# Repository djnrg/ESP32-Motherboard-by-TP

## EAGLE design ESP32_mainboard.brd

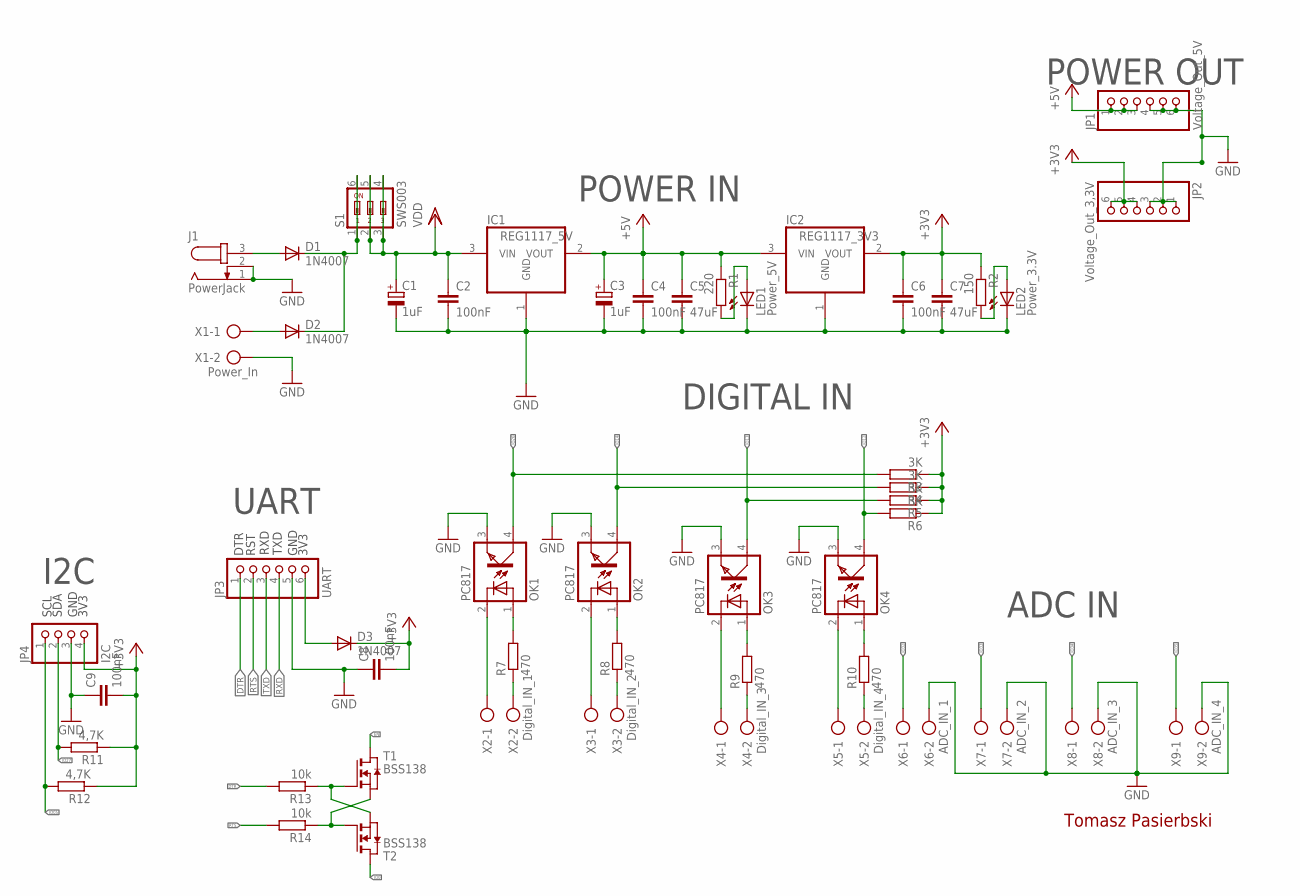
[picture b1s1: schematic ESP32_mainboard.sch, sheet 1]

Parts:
C1, C3: 1uF; 140CLH-0810
C2, C4, C6, C8, C9: 100nF; C1206
C5, C7: 47uF; C1808
D1, D2, D3: 1N4007; DO214AA
IC1: REG1117_5V; SOT223
IC2: REG1117_3V3; SOT223
J1: PowerJack; SPC4077
JP1: Voltage_Out_5V; 1X06/90
JP2: Voltage_Out_3,3V; 1X06/90
JP3: UART; 1X06/90
JP4: I2C; 1X04/90
LED1: Power_5V; CHIPLED_1206
LED2: Power_3.3V; CHIPLED_1206
OK1, OK2, OK3, OK4: PC817; DIL04
R1: 220; M1206
R2: 150; M1206
R3, R4, R5, R6: 3K; M1206
R7, R8, R9, R10: 470; M1206
R11, R12: 4,7K; M1206
R13, R14: 10k; M1206
S1: SWS003; SMS-003
T1, T2: BSS138; SOT-23
X1: Power_In; AK300/2
X2: Digital_IN_1; AK300/2
X3: Digital_IN_2; AK300/2
X4: Digital_IN_3; AK300/2
X5: Digital_IN_4; AK300/2
X6: ADC_IN_1; AK300/2
X7: ADC_IN_2; AK300/2
X8: ADC_IN_3; AK300/2
X9: ADC_IN_4; AK300/2

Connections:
+3V3: C6.1, C7.1, C8.2, C9.2, D3.C, IC2.2 (VOUT), JP2.4, JP2.5, JP2.6, JP4.4, R2.1, R3.1, R4.1, R5.1, R6.1, R11.1, R12.1; also elsewhere on the board
+5V: C3.+, C4.1, C5.1, IC1.2 (VOUT), IC2.3 (VIN), JP1.1, JP1.2, JP1.3, R1.1; also elsewhere on the board
DTR: JP3.1, R13.2
EN: T1.1 (D); also elsewhere on the board
GND: C1.-, C2.2, C3.-, C4.2, C5.2, C6.2, C7.2, C8.1, C9.1, IC1.1 (GND), IC2.1 (GND), J1.1, J1.2, JP1.4, JP1.5, JP1.6, JP2.1, JP2.2, JP2.3, JP3.5, JP4.3, LED1.C, LED2.C, OK1.3 (EMIT), OK2.3 (EMIT), OK3.3 (EMIT), OK4.3 (EMIT), X1.2, X6.2, X7.2, X8.2, X9.2; also elsewhere on the board
IO0: T2.1 (D); also elsewhere on the board
IO05: JP4.1, R12.2; also elsewhere on the board
IO12: OK4.4 (COL), R6.2; also elsewhere on the board
IO13: OK3.4 (COL), R5.2; also elsewhere on the board
IO14: OK2.4 (COL), R4.2; also elsewhere on the board
IO26: OK1.4 (COL), R3.2; also elsewhere on the board
IO27: JP4.2, R11.2; also elsewhere on the board
IO32: X6.1; also elsewhere on the board
IO33: X7.1; also elsewhere on the board
IO34: X8.1; also elsewhere on the board
IO35: X9.1; also elsewhere on the board
unnamed: D1.A, J1.3
unnamed: D1.C, D2.C, S1.1, S1.6
unnamed: D2.A, X1.1
unnamed: D3.A, JP3.6
unnamed: LED1.A, R1.2
unnamed: LED2.A, R2.2
unnamed: OK3.2 (C), X4.1
unnamed: OK3.1 (A), R9.2
unnamed: OK1.2 (C), X2.1
unnamed: R13.1, T1.3 (G), T2.2 (S)
unnamed: R14.1, T1.2 (S), T2.3 (G)
unnamed: R9.1, X4.2
unnamed: OK4.2 (C), X5.1
unnamed: OK4.1 (A), R10.2
unnamed: R10.1, X5.2
unnamed: OK2.2 (C), X3.1
unnamed: OK2.1 (A), R8.2
unnamed: R8.1, X3.2
unnamed: OK1.1 (A), R7.2
unnamed: R7.1, X2.2
RTS: JP3.2, R14.2
RXD: JP3.4; also elsewhere on the board
TXD: JP3.3; also elsewhere on the board
VDD: C1.+, C2.1, IC1.3 (VIN), S1.2, S1.3, S1.4, S1.5; also elsewhere on the board

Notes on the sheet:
I2C
UART
POWER OUT
POWER IN
ADC IN
DIGITAL IN
SDA
SCL
GND
3V3
RST
DTR
RXD
TXD
Tomasz Pasierbski

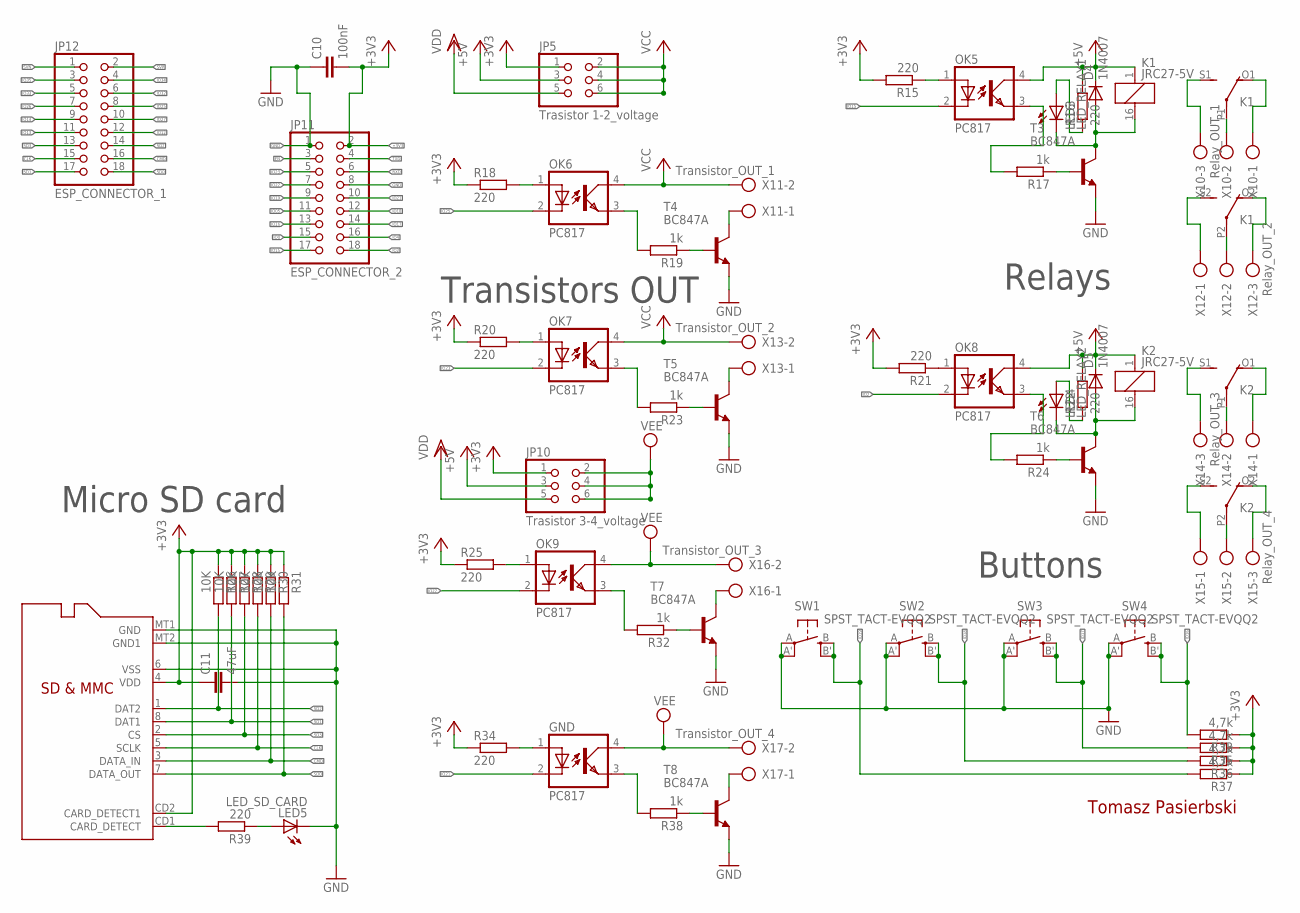
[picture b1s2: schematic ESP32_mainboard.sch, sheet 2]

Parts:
C10: 100nF; C1206
C11: 47uF; C1808
D4, D5: 1N4007; DO214AC
GND: PC817; DIL04
JP5: Trasistor 1-2_voltage; 2X03
JP10: Trasistor 3-4_voltage; 2X03
JP11: ESP_CONNECTOR_2; 2X09
JP12: ESP_CONNECTOR_1; 2X09
K1, K2: JRC27-5V; 351
LED3: LED_RELAY1; CHIPLED_1206
LED4: LED_RELAY2; CHIPLED_1206
LED5: LED_SD_CARD; CHIPLED_1206
OK5, OK6, OK7, OK8, OK9: PC817; DIL04
R15, R16, R18, R20, R21, R22, R25, R34, R39: 220; M1206
R17, R19, R23, R24, R32, R38: 1k; M1206
R26, R27, R28, R29, R30, R31: 10K; M1206
R33, R35, R36, R37: 4,7k; M1206
SW1, SW2, SW3, SW4: SPST_TACT-EVQQ2; EVQ-Q2
T3, T4, T5, T6, T7, T8: BC847A; SOT23-BEC
U2: MICROSD
X10: Relay_OUT_1; AK300/3
X11: Transistor_OUT_1; AK300/2
X12: Relay_OUT_2; AK300/3
X13: Transistor_OUT_2; AK300/2
X14: Relay_OUT_3; AK300/3
X15: Relay_OUT_4; AK300/3
X16: Transistor_OUT_3; AK300/2
X17: Transistor_OUT_4; AK300/2

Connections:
+3V3: C10.2, C11.1, JP5.1, JP10.1, JP11.2, R15.2, R18.1, R20.1, R21.2, R25.1, R26.1, R27.1, R28.1, R29.1, R30.1, R31.1, R33.1, R34.1, R35.1, R36.1, R37.1, U2.4 (VDD), U2.CD2 (CARD_DETECT1); also elsewhere on the board
+5V: D4.C, D5.C, JP5.3, JP10.3, K1.1, K2.1, OK5.4 (COL), OK8.4 (COL), R16.2, R22.2; also elsewhere on the board
CLK: JP12.15, R29.2, U2.5 (SCLK)
CMD: JP12.16, R30.2, U2.3 (DATA_IN)
EN: JP11.3; also elsewhere on the board
GND: C10.1, C11.2, JP11.1, JP11.8, LED5.C, SW1.A, SW1.A' (P1), SW2.A, SW2.A' (P1), SW3.A, SW3.A' (P1), SW4.A, SW4.A' (P1), T3.E, T4.E, T5.E, T6.E, T7.E, T8.E, U2.6 (VSS), U2.MT1 (GND), U2.MT2 (GND1); also elsewhere on the board
IO0: JP11.15; also elsewhere on the board
IO2: JP11.18, OK8.2 (C)
IO4: JP11.16
IO05: JP11.11; also elsewhere on the board
IO12: JP12.12; also elsewhere on the board
IO13: JP12.11; also elsewhere on the board
IO14: JP12.9; also elsewhere on the board
IO15: JP11.17, OK5.2 (C)
IO16: JP11.13, R33.2, SW4.B (S), SW4.B' (S1)
IO17: JP11.14, R35.2, SW3.B (S), SW3.B' (S1)
IO18: JP11.12, R36.2, SW2.B (S), SW2.B' (S1)
IO19: JP11.9, R37.2, SW1.B (S), SW1.B' (S1)
IO21: GND.2 (C), JP11.10
IO22: JP11.7, OK9.2 (C)
IO23: JP11.5, OK7.2 (C)
IO25: JP12.8, OK6.2 (C)
IO26: JP12.7; also elsewhere on the board
IO27: JP12.10; also elsewhere on the board
IO32: JP12.6; also elsewhere on the board
IO33: JP12.5; also elsewhere on the board
IO34: JP12.4; also elsewhere on the board
IO35: JP12.3; also elsewhere on the board
unnamed: K1.S1 (S), X10.3
unnamed: K1.O1 (O), X10.1
unnamed: K1.P1, X10.2
unnamed: K1.S2 (S), X12.1
unnamed: K1.P2, X12.2
unnamed: K1.O2 (O), X12.3
unnamed: K2.O1 (O), X14.1
unnamed: K2.S1 (S), X14.3
unnamed: K2.P1, X14.2
unnamed: K2.S2 (S), X15.1
unnamed: K2.O2 (O), X15.3
unnamed: K2.P2, X15.2
unnamed: OK8.1 (A), R21.1
unnamed: OK5.1 (A), R15.1
unnamed: R17.1, T3.B
unnamed: OK5.3 (EMIT), R17.2
unnamed: OK8.3 (EMIT), R24.2
unnamed: D4.A, K1.16 (2), LED3.C, T3.C
unnamed: R24.1, T6.B
unnamed: LED3.A, R16.1
unnamed: OK6.1 (A), R18.2
unnamed: OK7.1 (A), R20.2
unnamed: D5.A, K2.16 (2), LED4.C, T6.C
unnamed: LED4.A, R22.1
unnamed: R19.1, T4.B
unnamed: OK6.3 (EMIT), R19.2
unnamed: R39.2, U2.CD1 (CARD_DETECT)
unnamed: T4.C, X11.1
unnamed: R23.1, T5.B
unnamed: OK7.3 (EMIT), R23.2
unnamed: T5.C, X13.1
unnamed: LED5.A, R39.1
unnamed: OK9.1 (A), R25.2
unnamed: R32.1, T7.B
unnamed: OK9.3 (EMIT), R32.2
unnamed: T7.C, X16.1
unnamed: GND.1 (A), R34.2
unnamed: R38.1, T8.B
unnamed: GND.3 (EMIT), R38.2
unnamed: T8.C, X17.1
RXD: JP11.6; also elsewhere on the board
SD0: JP12.18, R31.2, U2.7 (DATA_OUT)
SD1: JP12.17, R27.2, U2.8 (DAT1)
SD2: JP12.14, R26.2, U2.1 (DAT2)
SD3: JP12.13, R28.2, U2.2 (CS)
SVN: JP12.1
SVP: JP12.2
TXD: JP11.4; also elsewhere on the board
VCC: JP5.2, JP5.4, JP5.6, OK6.4 (COL), OK7.4 (COL), X11.2, X13.2
VDD: JP5.5, JP10.5; also elsewhere on the board
VEE: GND.4 (COL), JP10.2, JP10.4, JP10.6, OK9.4 (COL), X16.2, X17.2

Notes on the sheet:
Buttons
Relays
Transistors OUT
Micro SD card
Tomasz Pasierbski

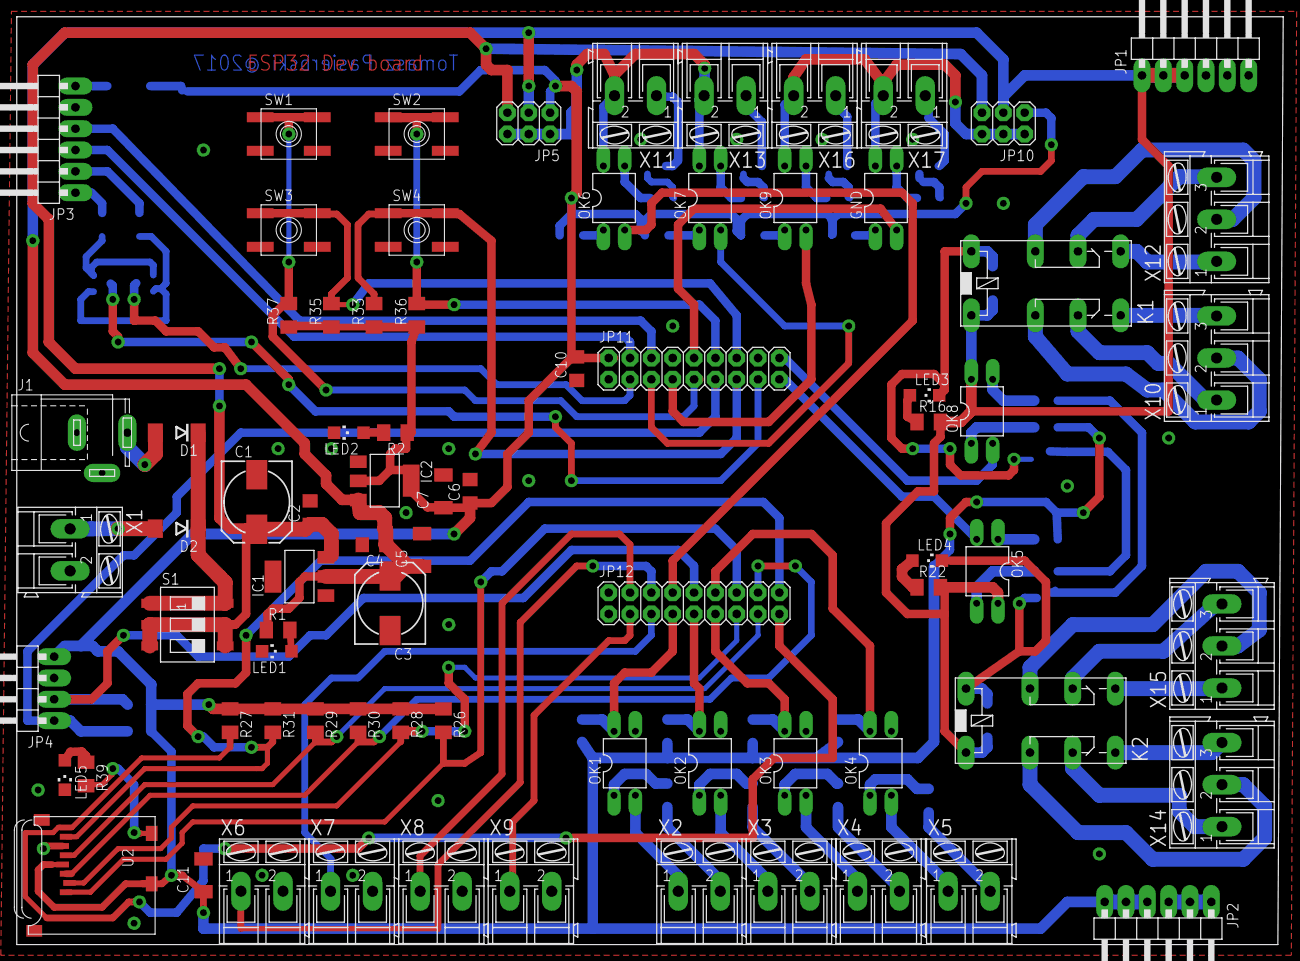
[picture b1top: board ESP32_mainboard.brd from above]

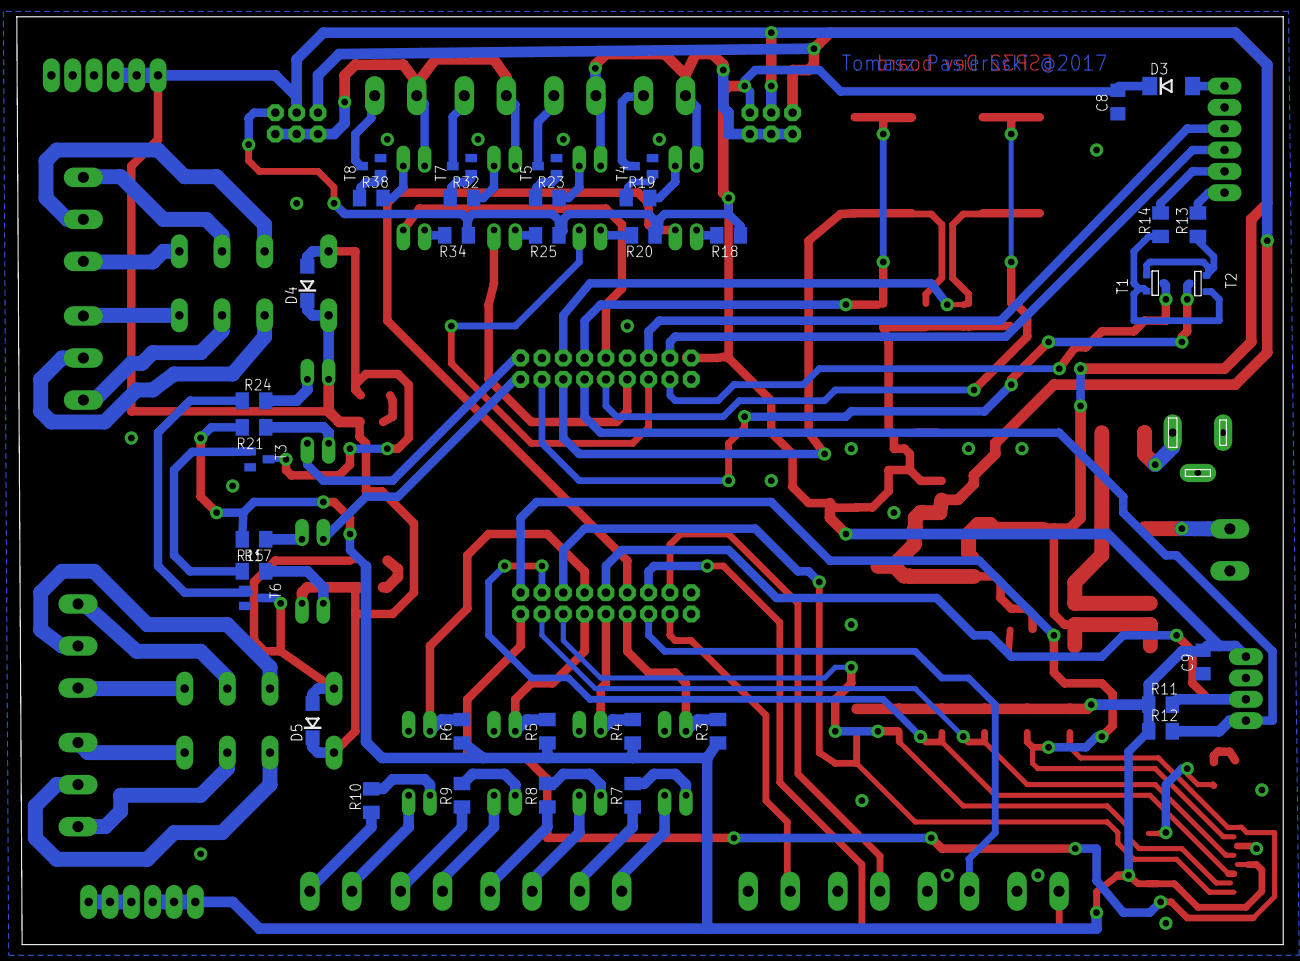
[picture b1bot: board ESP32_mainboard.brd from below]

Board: 2 copper layers, 150.8 x 110.5 mm, 114 parts (37 on the bottom side), 98 nets.

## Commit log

2018-12-01 Initialize upload
    Last version before manufacturing
2018-12-01 Revert "Initialize upload"
    This reverts commit ad7130b4597513a31f529159903ec4896dc0400f.
2018-12-01 Revert "Revert "Initialize upload""
    This reverts commit e7bd11064f78094730e2ae7fc94e34dc39cdb713.
